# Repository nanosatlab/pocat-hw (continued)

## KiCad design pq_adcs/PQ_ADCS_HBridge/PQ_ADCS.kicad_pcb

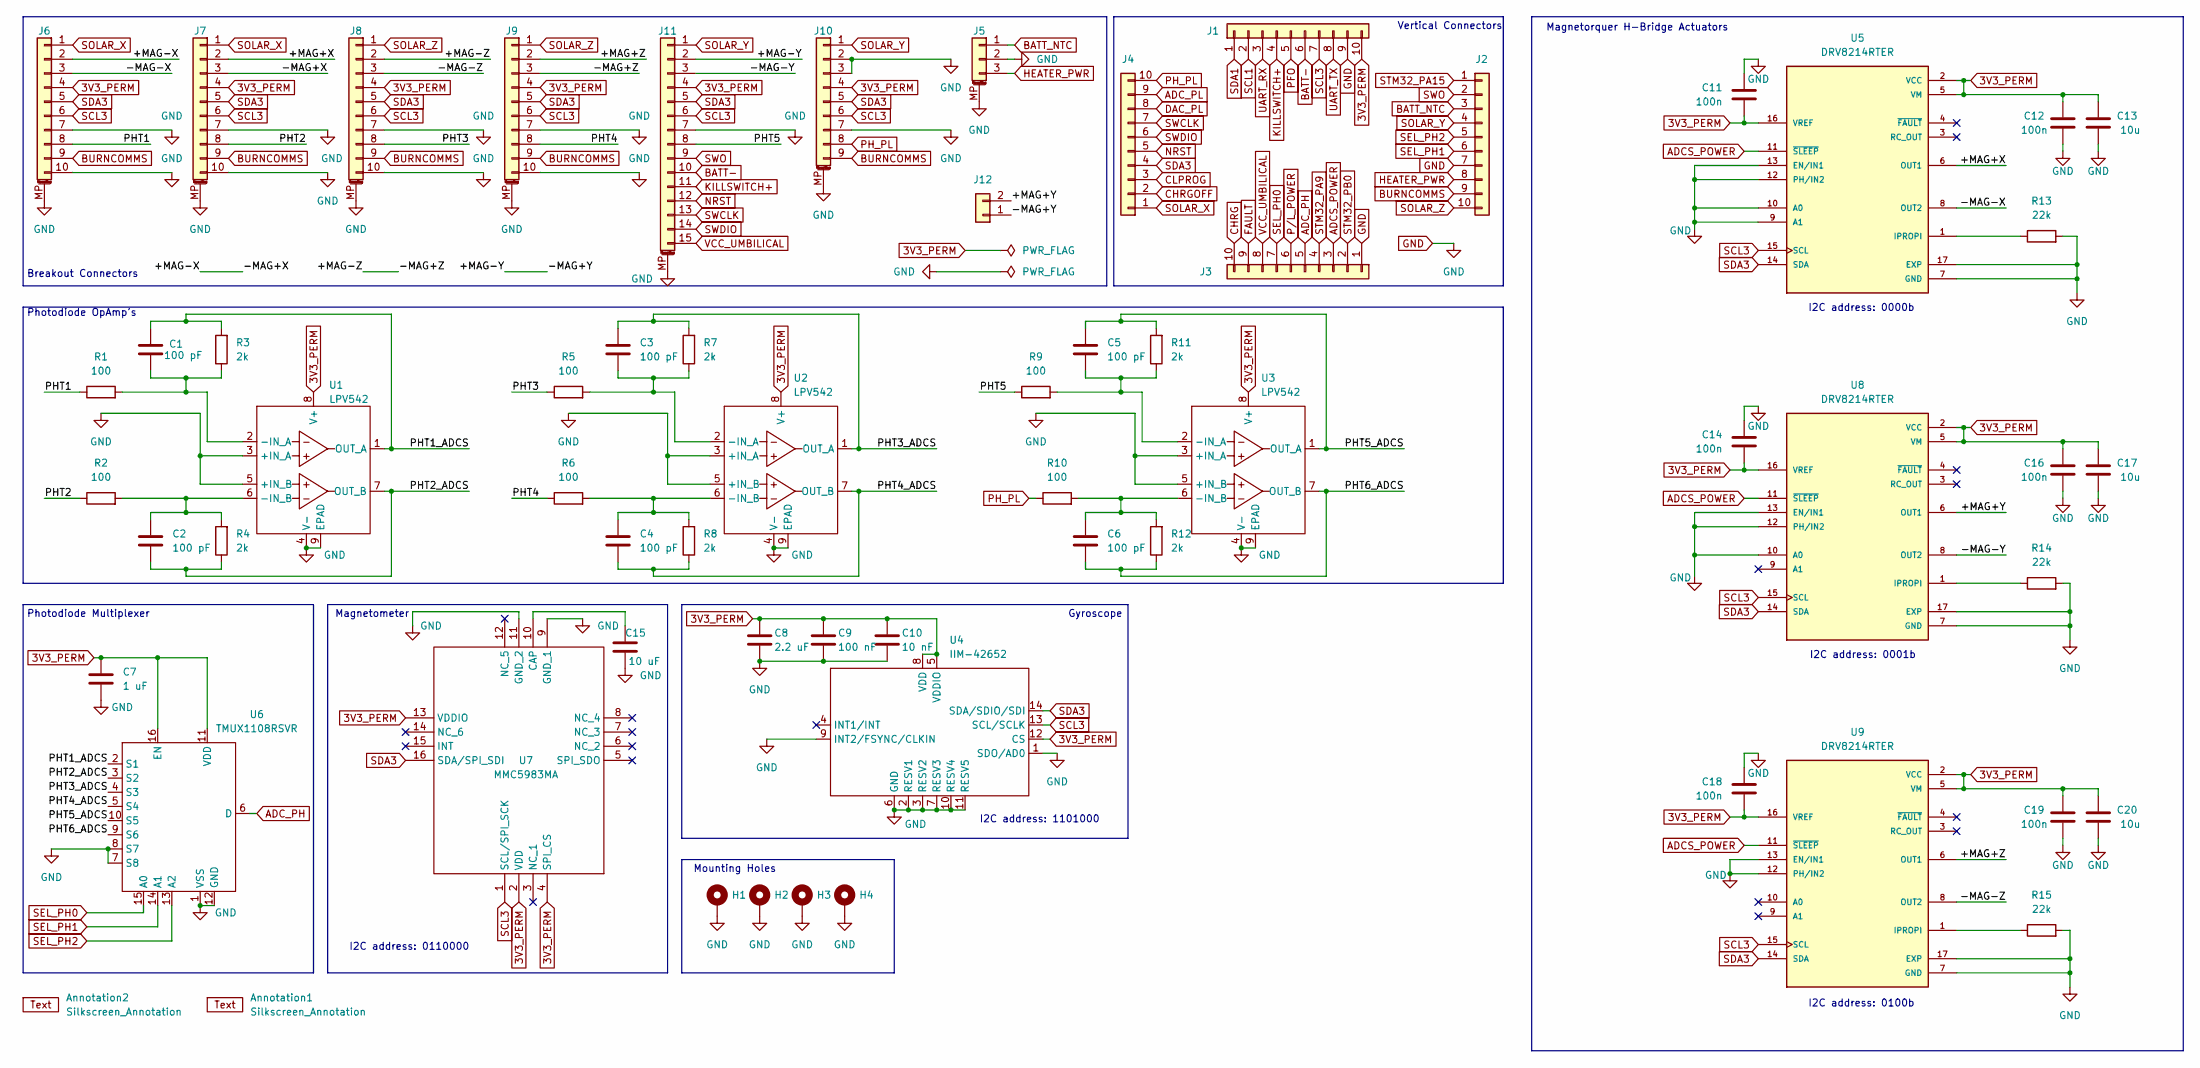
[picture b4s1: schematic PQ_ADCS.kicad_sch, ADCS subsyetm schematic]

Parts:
Annotation1: Silkscreen_Annotation; Bike
Annotation2: Silkscreen_Annotation; Bridgemaker
C1, C2, C3, C4, C5, C6: 100 pF; C_0603_1608Metric; Manufacturer Part Numbe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 06035C101K4T2A
C7: 1 uF; C_0603_1608Metric; Manufacturer Part Numbe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 GRM188R61A105KA61D
C8: 2.2 uF; C_0603_1608Metric; Manufacturer Part Numbe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 GRM033R60J225ME15D
C9: 100 nF; C_0603_1608Metric; Manufacturer Part Numbe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 GRM188R72A104KA35J
C10: 10 nF; C_0603_1608Metric; Manufacturer Part Numbe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 0201YD103KAT4A
C11, C12, C14, C16, C18, C19: 100n; C_0603_1608Metric
C13, C17, C20: 10u; C_0603_1608Metric
C15: 10 uF; C_0805_2012Metric; Manufacturer Part Numbe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 GRM188R72A104KA35J
H1, H2, H3, H4: MountingHole_Pad; MountingHole_3.2mm_M3_Pad; Manufacturer Part Numbe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 N/A
J1, J2, J3, J4: CES-110-02-L-S; SLW-110-01; Manufacturer Part Numbe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 CES-110-02-L-S
J5: Pico-Clasp_01x03; Picoclasp03; Manufacturer Part Numbe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 203556-0307
J6, J7, J8, J9: Pico-Clasp_01x10; Picoclasp10; Manufacturer Part Numbe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 504449-1007
J10: Pico-Clasp_01x09; Picoclasp09; Manufacturer Part Numbe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 504449-0907
J11: Pico-Clasp_01x15; Picoclasp15; Manufacturer Part Numbe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 504449-1507
J12: CES-102-02-L-S; CES-102-02; Manufacturer Part Numbe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 CES-102-02-L-S
R1, R2, R5, R6, R9, R10: 100; R_0603_1608Metric; Manufacturer Part Numbe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 AC0603FR-13100RL
R3, R4, R7, R8, R11, R12: 2k; R_0603_1608Metric; Manufacturer Part Numbe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 RC0603FR-132KL
R13, R14, R15: 22k; R_0603_1608Metric; Manufacturer Part Numbe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 AC0603FR-13100RL
U1, U2, U3: LPV542; TI_X1SON-8_3x3mm; Manufacturer Part Numbe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 LPV542DNXR
U4: IIM-42652; IIM42652; Manufacturer_Part_Number IIM-42652; Mouser Part Number 410-IIM-42652
U5, U8, U9: DRV8214RTER; IC_DRV8214RTER; PARTREV November 2023
U6: TMUX1108RSVR; UQFN-16_1.8x2.6_Pitch0.4mm; Manufacturer Part Numbe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 TMUX1108RSVR
U7: MMC5983MA; Manufacturer_Part_Number MMC5983MA; Mouser Part Number 438-MMC5983MA

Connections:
3V3_PERM: C7.1, C8.1, C9.1, C10.1, C11.2, C12.1, C13.1, C14.2, C16.1, C17.1, C18.2, C19.1, C20.1, J1.10, J6.4, J7.4, J8.4, J9.4, J10.4, J11.4, U1.8 (V+), U2.8 (V+), U3.8 (V+), U4.5 (VDDIO), U4.8 (VDD), U4.12 (CS), U5.2 (VCC), U5.5 (VM), U5.16 (VREF), U6.11 (VDD), U6.16 (EN), U7.2 (VDD), U7.4 (SPI_CS), U7.13 (VDDIO), U8.2 (VCC), U8.5 (VM), U8.16 (VREF), U9.2 (VCC), U9.5 (VM), U9.16 (VREF)
/+MAG+X: J7.2, U5.6 (OUT1)
/+MAG+Y: J12.2, U8.6 (OUT1)
/+MAG+Z: J9.2, U9.6 (OUT1)
/+MAG-X: J6.2, J7.3
/+MAG-Y: J11.2, J12.1
/+MAG-Z: J8.2, J9.3
/-MAG-X: J6.3, U5.8 (OUT2)
/-MAG-Y: J11.3, U8.8 (OUT2)
/-MAG-Z: J8.3, U9.8 (OUT2)
/PHT1: J6.8, R1.1
/PHT1_ADCS: C1.1, R3.2, U1.1 (OUT_A), U6.2 (S1)
/PHT2: J7.8, R2.1
/PHT2_ADCS: C2.2, R4.1, U1.7 (OUT_B), U6.3 (S2)
/PHT3: J8.8, R5.1
/PHT3_ADCS: C3.1, R7.2, U2.1 (OUT_A), U6.4 (S3)
/PHT4: J9.8, R6.1
/PHT4_ADCS: C4.2, R8.1, U2.7 (OUT_B), U6.5 (S4)
/PHT5: J11.8, R9.1
/PHT5_ADCS: C5.1, R11.2, U3.1 (OUT_A), U6.10 (S5)
/PHT6_ADCS: C6.2, R12.1, U3.7 (OUT_B), U6.9 (S6)
ADCS_POWER: J3.3, U5.11 (~SLEEP), U8.11 (~SLEEP), U9.11 (~SLEEP)
ADC_PH: J3.5, U6.6 (D)
ADC_PL: J4.9
BATT-: J1.6, J11.10
BATT_NTC: J2.3, J5.1
BURNCOMMS: J2.9, J6.9, J7.9, J8.9, J9.9, J10.9
CHRG: J3.10
CHRGOFF: J4.2
CLPROG: J4.3
DAC_PL: J4.8
FAULT: J3.9
GND: C7.2, C8.2, C9.2, C10.2, C11.1, C12.2, C13.2, C14.1, C15.2, C16.2, C17.2, C18.1, C19.2, C20.2, H1.1, H2.1, H3.1, H4.1, J1.9, J2.7, J3.1, J5.2, J5.MP, J6.7, J6.10, J6.MP, J7.7, J7.10, J7.MP, J8.7, J8.10, J8.MP, J9.7, J9.10, J9.MP, J10.2, J10.3, J10.7, J10.MP, J11.7, J11.MP, R13.2, R14.2, R15.2, U1.3 (+IN_A), U1.4 (V-), U1.5 (+IN_B), U1.9 (EPAD), U2.3 (+IN_A), U2.4 (V-), U2.5 (+IN_B), U2.9 (EPAD), U3.3 (+IN_A), U3.4 (V-), U3.5 (+IN_B), U3.9 (EPAD), U4.1 (SDO/AD0), U4.2 (RESV1), U4.3 (RESV2), U4.6 (GND), U4.7 (RESV3), U4.9 (INT2/FSYNC/CLKIN), U4.10 (RESV4), U4.11 (RESV5), U5.7 (GND), U5.9 (A1), U5.10 (A0), U5.12 (PH/IN2), U5.13 (EN/IN1), U5.17 (EXP), U6.1 (VSS), U6.7 (S8), U6.8 (S7), U6.12 (GND), U7.9 (GND_1), U7.11 (GND_2), U8.7 (GND), U8.10 (A0), U8.12 (PH/IN2), U8.13 (EN/IN1), U8.17 (EXP), U9.7 (GND), U9.12 (PH/IN2), U9.13 (EN/IN1), U9.17 (EXP)
HEATER_PWR: J2.8, J5.3
KILLSWITCH+: J1.4, J11.11
NRST: J4.5, J11.12
unnamed: C1.2, R1.2, R3.1, U1.2 (-IN_A)
unnamed: C2.1, R2.2, R4.2, U1.6 (-IN_B)
unnamed: C3.2, R5.2, R7.1, U2.2 (-IN_A)
unnamed: C4.1, R6.2, R8.2, U2.6 (-IN_B)
unnamed: C5.2, R9.2, R11.1, U3.2 (-IN_A)
unnamed: C6.1, R10.2, R12.2, U3.6 (-IN_B)
unnamed: R13.1, U5.1 (IPROPI)
unnamed: C15.1, U7.10 (CAP)
unnamed: R14.1, U8.1 (IPROPI)
unnamed: R15.1, U9.1 (IPROPI)
PFO: J1.5
PH_PL: J4.10, J10.8, R10.1
P/L_POWER: J3.6
SCL1: J1.2
SCL3: J1.7, J6.6, J7.6, J8.6, J9.6, J10.6, J11.6, U4.13 (SCL/SCLK), U5.15 (SCL), U7.1 (SCL/SPI_SCK), U8.15 (SCL), U9.15 (SCL)
SDA1: J1.1
SDA3: J4.4, J6.5, J7.5, J8.5, J9.5, J10.5, J11.5, U4.14 (SDA/SDIO/SDI), U5.14 (SDA), U7.16 (SDA/SPI_SDI), U8.14 (SDA), U9.14 (SDA)
SEL_PH0: J3.7, U6.15 (A0)
SEL_PH1: J2.6, U6.14 (A1)
SEL_PH2: J2.5, U6.13 (A2)
SOLAR_X: J4.1, J6.1, J7.1
SOLAR_Y: J2.4, J10.1, J11.1
SOLAR_Z: J2.10, J8.1, J9.1
STM32_PA9: J3.4
STM32_PA15: J2.1
STM32_PB0: J3.2
SWCLK: J4.7, J11.13
SWDIO: J4.6, J11.14
SWO: J2.2, J11.9
UART_RX: J1.3
UART_TX: J1.8
VCC_UMBILICAL: J3.8, J11.15

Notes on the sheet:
I2C address: 0100b
Mounting Holes
Breakout Connectors
I2C address: 1101000
Photodiode Multiplexer
Gyroscope
I2C address: 0000b
I2C address: 0110000
I2C address: 0001b
Photodiode OpAmp's
Magnetorquer H-Bridge Actuators
Vertical Connectors
Magnetometer

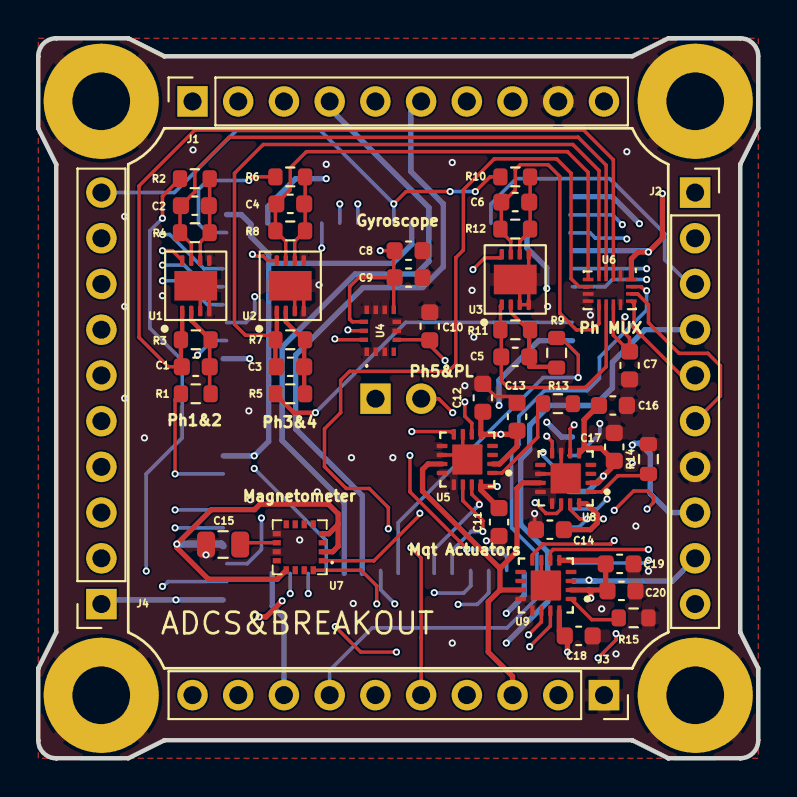
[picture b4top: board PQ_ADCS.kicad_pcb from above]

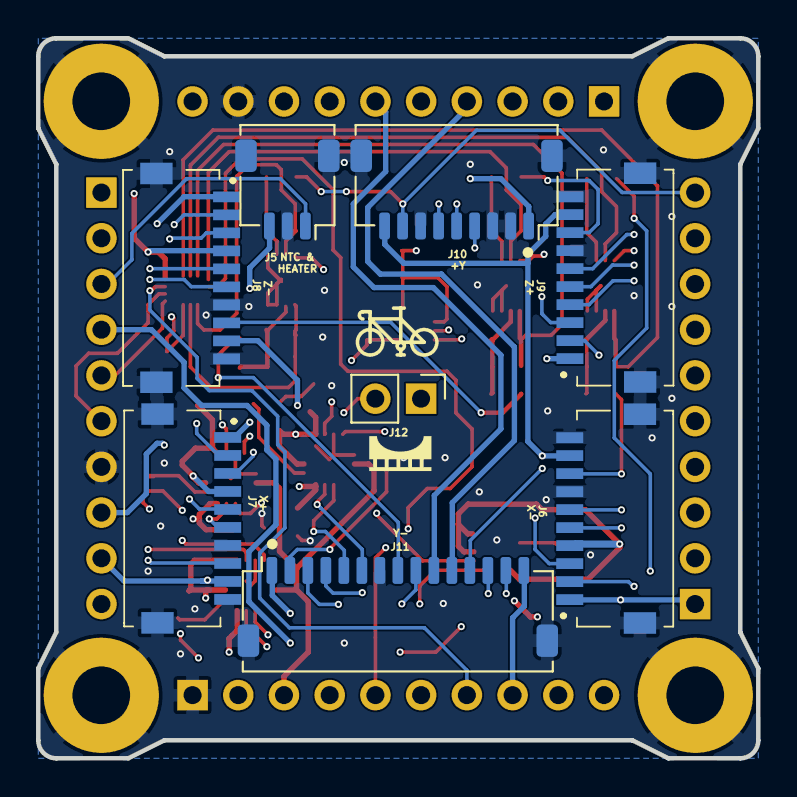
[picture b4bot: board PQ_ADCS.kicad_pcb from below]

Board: 6 copper layers, 40.0 x 40.0 mm, 62 parts (10 on the bottom side), 53 nets.

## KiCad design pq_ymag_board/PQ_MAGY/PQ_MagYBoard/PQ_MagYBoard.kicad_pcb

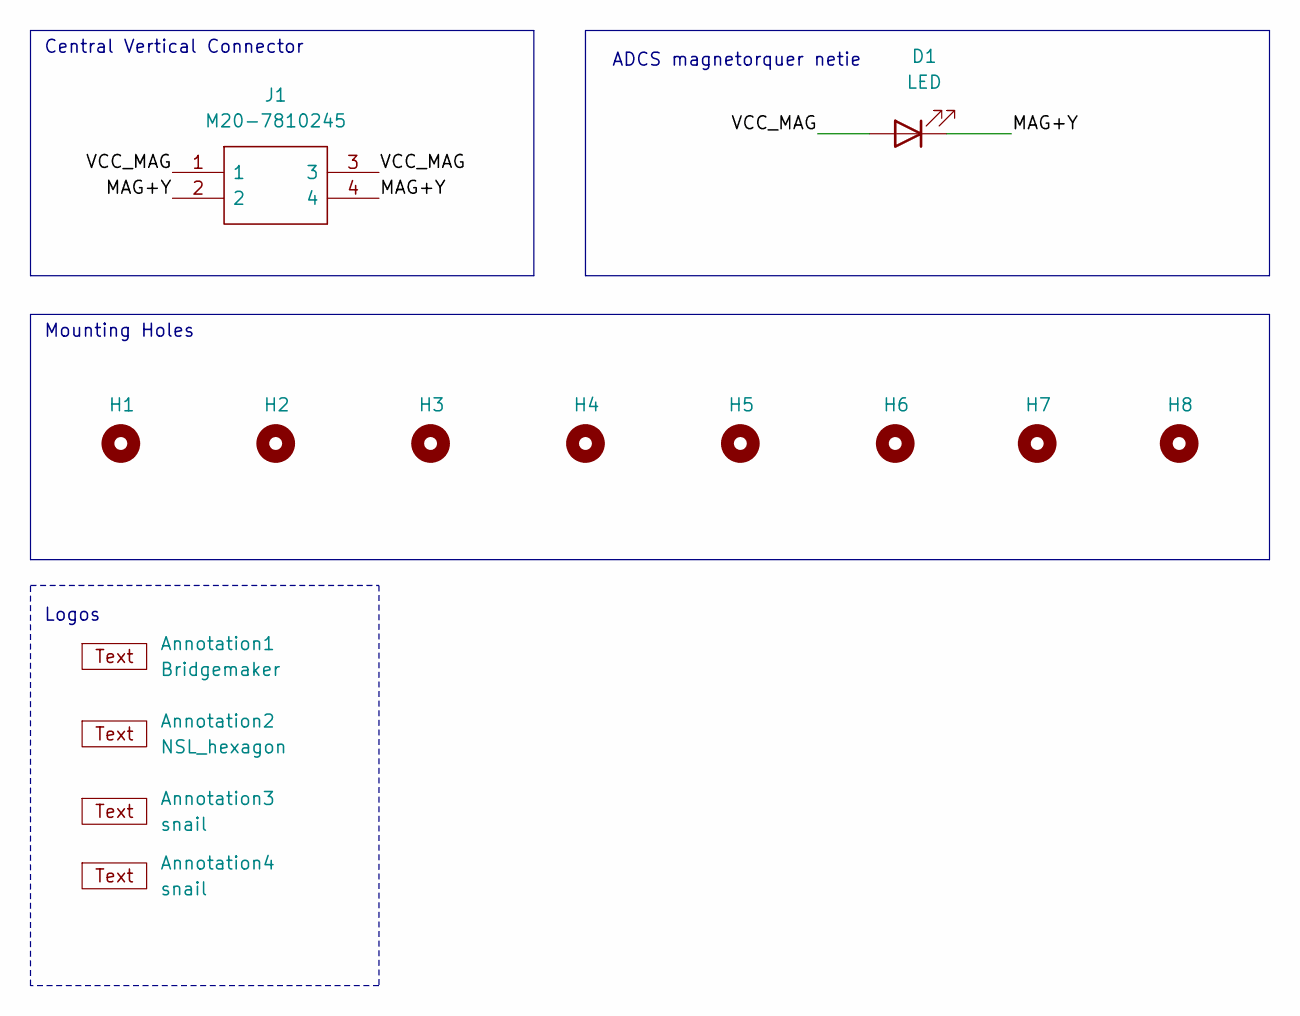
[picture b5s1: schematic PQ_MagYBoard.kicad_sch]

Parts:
Annotation1: Bridgemaker
Annotation2: NSL_hexagon
Annotation3: snail; Snail
Annotation4: snail; pocat_lektron
D1: LED; LED_0402_1005Metric
H1, H2, H3, H4: MountingHole; MountingHole_6.4mm_M6_DIN965
H5, H6, H7, H8: MountingHole; MountingHole_2.2mm_M2_DIN965
J1: M20-7810245; M207810245; Manufacturer_Part_Number M20-7810245; Mouser Part Number 855-M20-7810245

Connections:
/MAG+Y: D1.1 (K), J1.2, J1.4
/VCC_MAG: D1.2 (A), J1.1, J1.3

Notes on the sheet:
Logos
Mounting Holes
ADCS magnetorquer netie
Central Vertical Connector

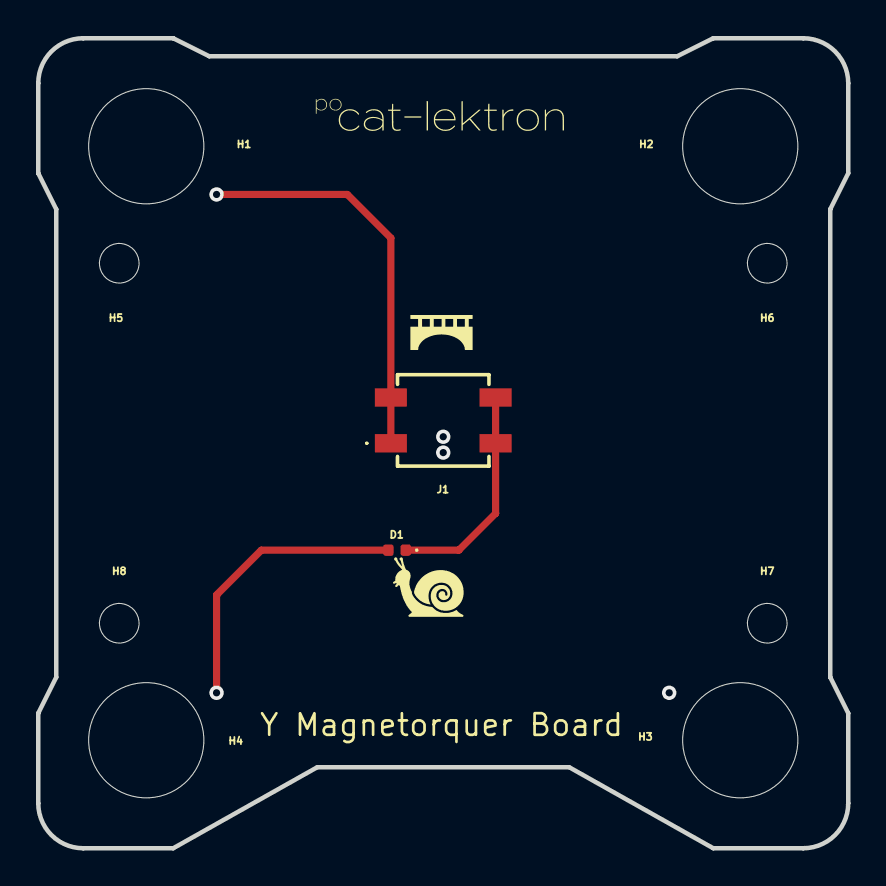
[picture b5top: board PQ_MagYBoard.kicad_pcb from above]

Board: 6 copper layers, 45.0 x 45.0 mm, 14 parts (1 on the bottom side), 2 nets.

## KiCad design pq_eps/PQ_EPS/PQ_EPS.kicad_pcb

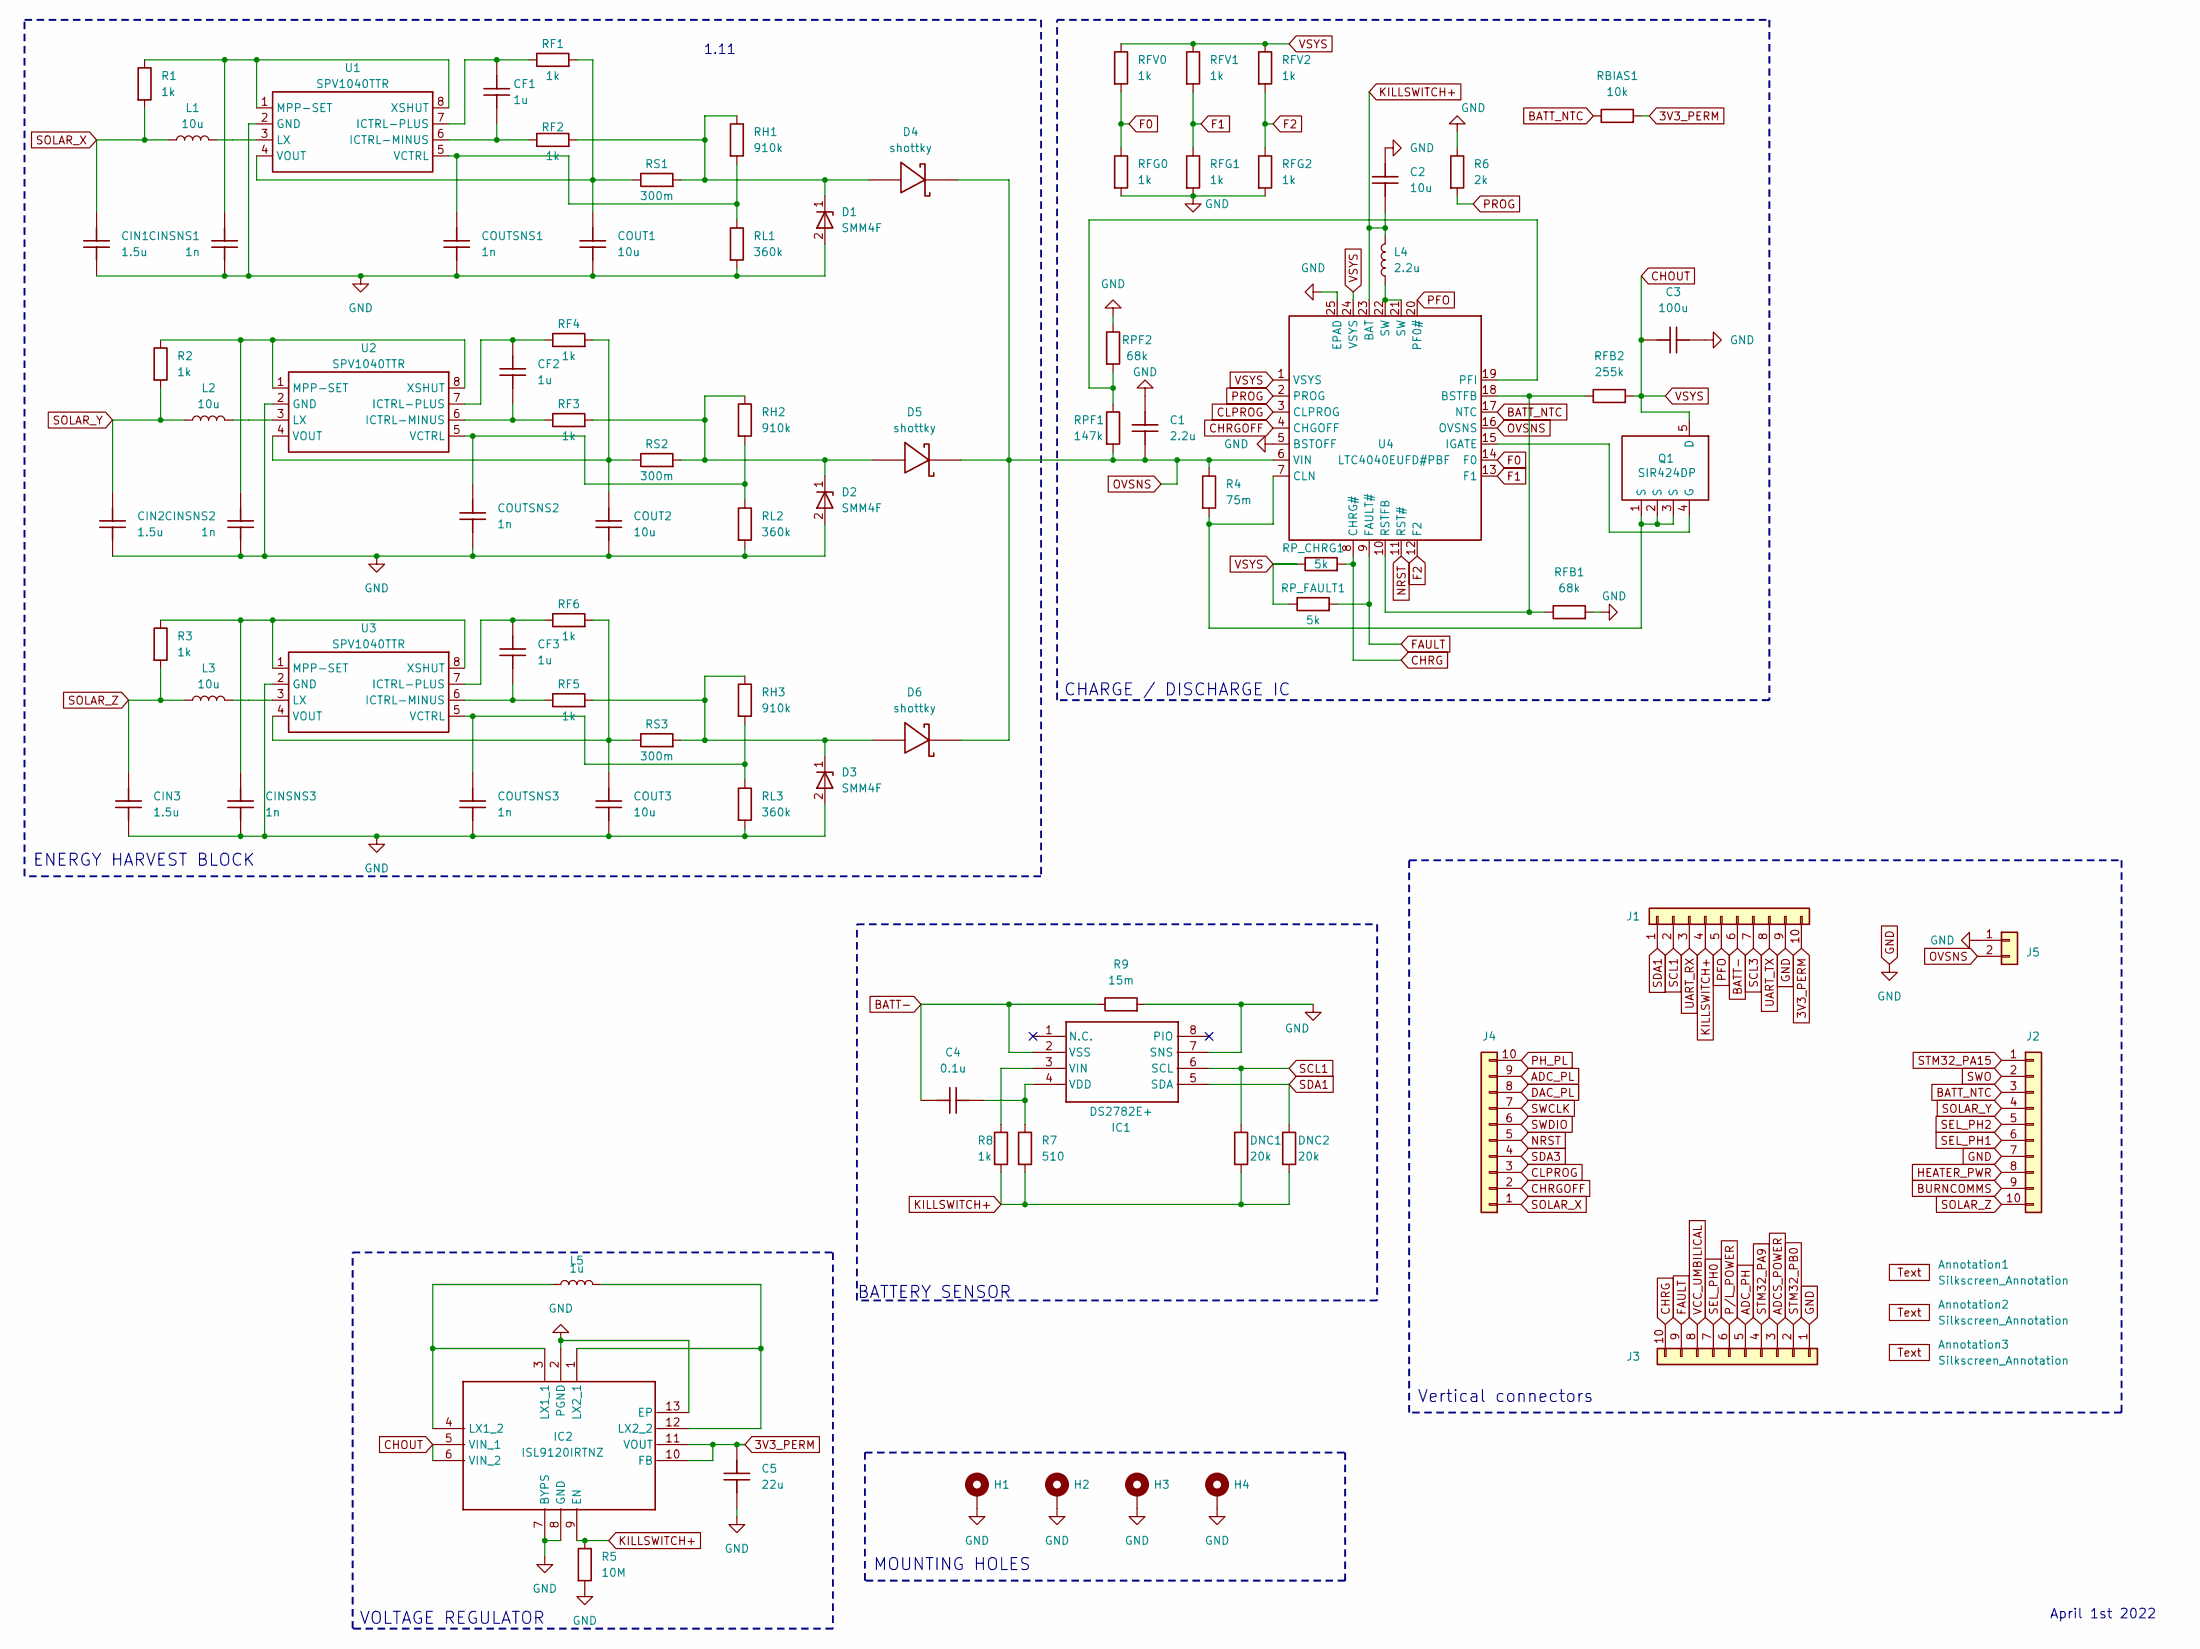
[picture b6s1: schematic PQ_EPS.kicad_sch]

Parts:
Annotation1: Silkscreen_Annotation; Bridgemaker
Annotation2: Silkscreen_Annotation; NakNak
Annotation3: Silkscreen_Annotation; Snail
C1: 2.2u; C_0603_1608Metric; Manufacturer Part Numbe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 GRM155R61C225KE11D
C2: 10u; C_0603_1608Metric; Manufacturer Part Numbe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 GRM188R61A106KAALD
C3: 100u; C_1206_3216Metric; Manufacturer Part Numbe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 GRM21BR60J107ME15K
C4: 0.1u; C_0603_1608Metric; Manufacturer Part Numbe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 C0603C104K8PACTU
C5: 22u; C_0603_1608Metric; Manufacturer Part Numbe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 GRM187R61A226ME15J
CF1, CF2, CF3: 1u; C_0603_1608Metric; Manufacturer Part Numbe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 GRM155R61C105KA12D
CIN1, CIN2, CIN3: 1.5u; C_0603_1608Metric; Manufacturer Part Numbe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 C1005X5R1V155K050BC
CINSNS1, CINSNS2, CINSNS3: 1n; C_0603_1608Metric; Manufacturer Part Numbe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 GRM155R61A102KA01D
COUT1, COUT2, COUT3: 10u; C_0603_1608Metric; Manufacturer Part Numbe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 GRM188R61A106KAALD
COUTSNS1, COUTSNS2, COUTSNS3: 1n; C_0603_1608Metric; Manufacturer Part Numbe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 GRM155R61A102KA01D
D1, D2, D3: SMM4F; SMM4F15ATR; Manufacturer Part Numbe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 SMM4F18A-TR
D4, D5, D6: shottky; RBS1LAM40ATR_Schottky; Manufacturer Part Numbe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 RBS1LAM40ATR
DNC1, DNC2: 20k; R_0603_1608Metric; Manufacturer Part Numbe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 ERJ-UP3J203V
H1, H2, H3, H4: MountingHole_Pad; MountingHole_3.2mm_M3_Pad; Manufacturer Part Numbe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 N/A
IC1: DS2782E+; TSSOP-8_4.4x3mm_P0.65mm; Manufacturer Part Numbe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 DS2782E+
IC2: ISL9120IRTNZ; Manufacturer Part Numbe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 ISL9120IRTNZ
J1, J2, J3, J4: CES-110-02-L-S; SLW-110-01; Manufacturer Part Numbe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 CES-110-02-L-S
J5: CES-102-02
L1, L2, L3: 10u; L_0805_2012Metric; Manufacturer Part Numbe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 LQH2MPZ100MGRL
L4: 2.2u; XAL5030222MEC; Manufacturer_Part_Number XAL5030-222MEC; Mouser Part Number 994-XAL5030-222MEC
L5: 1u; L_0805_2012Metric; Manufacturer Part Numbe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 TFM201610GHM1R0A
Q1: SIR424DP; Manufacturer Part Numbe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 SIR424DP-T1-GE3
R1, R2, R3, R8: 1k; R_0603_1608Metric
R4: 75m; R_0805_2012Metric; Manufacturer Part Numbe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 UR73V2ATTD75L0F
R5: 10M; R_0805_2012Metric; Manufacturer Part Numbe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 UR73V2ATTD75L0F
R6: 2k; R_0603_1608Metric
R7: 510; R_0603_1608Metric
R9: 15m; R_0603_1608Metric
RBIAS1: 10k; R_0603_1608Metric
RF1, RF2, RF3, RF4, RF5, RF6: 1k; R_0603_1608Metric; Manufacturer Part Numbe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 CRCW04021K00FKEDHP
RFB1: 68k; R_0603_1608Metric; Manufacturer Part Numbe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 SG73P1ETTP6802F
RFB2: 255k; R_0402_1005Metric; Manufacturer Part Numbe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 ERJ-U02F2553X
RFG0, RFG1, RFG2: 1k; R_0603_1608Metric; Manufacturer Part Numbe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 PCAN0805E1001BST5
RFV0, RFV1, RFV2: 1k; R_0603_1608Metric; Manufacturer Part Numbe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 PCAN0805E1001BST5
RH1, RH2, RH3: 910k; R_0603_1608Metric; Manufacturer Part Numbe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 ERJ-PA3F9103V
RL1, RL2, RL3: 360k; R_0603_1608Metric; Manufacturer Part Numbe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 ERJ-UP3F3603V
RPF1: 147k; R_0603_1608Metric; Manufacturer Part Numbe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 ERJ-P03F1473V
RPF2: 68k; R_0603_1608Metric; Manufacturer Part Numbe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 SG73P1ETTP6802F
RP_CHRG1: 5k; R_0805_2012Metric; Manufacturer Part Numbe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 CRCW08055K00JNTA
RP_FAULT1: 5k; R_0805_2012Metric; Manufacturer Part Numbe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 CRCW08055K00JNTA
RS1, RS2, RS3: 300m; R_0603_1608Metric; Manufacturer Part Numbe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 UCR03EVPFLR300
U1, U2, U3: SPV1040TTR; TSSOP-8_4.4x3mm_P0.65mm; Manufacturer Part Numbe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 SPV1040TTR
U4: LTC4040EUFD#PBF; QFN-24-1EP_4x5mm_P0.5mm_EP2.65x3.65mm; Manufacturer Part Numbe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 LTC4040IUFD#PBF

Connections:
3V3_PERM: C5.2, IC2.10 (FB), IC2.11 (VOUT), J1.10, RBIAS1.2
ADCS_POWER: J3.3
ADC_PH: J3.5
ADC_PL: J4.9
BATT-: C4.2, IC1.2 (VSS), J1.6, R9.1
BATT_NTC: J2.3, RBIAS1.1, U4.17 (NTC)
BURNCOMMS: J2.9
CHOUT: C3.1, IC2.5 (VIN_1), IC2.6 (VIN_2), Q1.5 (D), RFB2.2, RFV0.1, RFV1.1, RFV2.1, RP_CHRG1.1, RP_FAULT1.1, U4.1 (VSYS), U4.24 (VSYS)
CHRG: J3.10, RP_CHRG1.2, U4.8 (CHRG#)
CHRGOFF: J4.2, U4.4 (CHGOFF)
CLPROG: J4.3, U4.3 (CLPROG)
DAC_PL: J4.8
F0: RFG0.1, RFV0.2, U4.14 (F0)
F1: RFG1.1, RFV1.2, U4.13 (F1)
F2: RFG2.1, RFV2.2, U4.12 (F2)
FAULT: J3.9, RP_FAULT1.2, U4.9 (FAULT#)
GND: C1.2, C2.2, C3.2, C5.1, CIN1.1, CIN2.1, CIN3.1, CINSNS1.1, CINSNS2.1, CINSNS3.1, COUT1.1, COUT2.1, COUT3.1, COUTSNS1.1, COUTSNS2.1, COUTSNS3.1, D1.2, D2.2, D3.2, H1.1, H2.1, H3.1, H4.1, IC1.7 (SNS), IC2.2 (PGND), IC2.7 (BYPS), IC2.8 (GND), IC2.13 (EP), J1.9, J2.7, J3.1, J5.1, R5.2, R6.1, R9.2, RFB1.2, RFG0.2, RFG1.2, RFG2.2, RL1.2, RL2.2, RL3.2, RPF2.1, U1.2 (GND), U2.2 (GND), U3.2 (GND), U4.5 (BSTOFF), U4.25 (EPAD)
HEATER_PWR: J2.8
KILLSWITCH+: C2.1, DNC1.2, DNC2.2, IC2.9 (EN), J1.4, L4.2, R5.1, R7.2, R8.2, U4.23 (BAT)
NRST: J4.5, U4.11 (RST#)
unnamed: D1.1, D4.2, RF2.2, RH1.1, RS1.2
unnamed: D2.1, D5.2, RF3.2, RH2.1, RS2.2
unnamed: D3.1, D6.2, RF5.2, RH3.1, RS3.2
unnamed: C4.1, IC1.4 (VDD), R7.1
unnamed: IC1.3 (VIN), R8.1
unnamed: IC2.3 (LX1_1), IC2.4 (LX1_2), L5.1
unnamed: IC2.1 (LX2_1), IC2.12 (LX2_2), L5.2
unnamed: L4.1, U4.21 (SW), U4.22 (SW)
unnamed: Q1.4 (G), U4.15 (IGATE)
unnamed: CF1.1, RF2.1, U1.6 (ICTRL-MINUS)
unnamed: CF1.2, RF1.1, U1.7 (ICTRL-PLUS)
unnamed: L1.1, U1.3 (LX)
unnamed: CINSNS1.2, R1.1, U1.1 (MPP-SET), U1.8 (XSHUT)
unnamed: COUTSNS1.2, RH1.2, RL1.1, U1.5 (VCTRL)
unnamed: COUT1.2, RF1.2, RS1.1, U1.4 (VOUT)
unnamed: CF2.1, RF3.1, U2.6 (ICTRL-MINUS)
unnamed: CF2.2, RF4.1, U2.7 (ICTRL-PLUS)
unnamed: L2.2, U2.3 (LX)
unnamed: CINSNS2.2, R2.1, U2.1 (MPP-SET), U2.8 (XSHUT)
unnamed: COUTSNS2.2, RH2.2, RL2.1, U2.5 (VCTRL)
unnamed: COUT2.2, RF4.2, RS2.1, U2.4 (VOUT)
unnamed: CF3.1, RF5.1, U3.6 (ICTRL-MINUS)
unnamed: CF3.2, RF6.1, U3.7 (ICTRL-PLUS)
unnamed: L3.2, U3.3 (LX)
unnamed: CINSNS3.2, R3.1, U3.1 (MPP-SET), U3.8 (XSHUT)
unnamed: COUTSNS3.2, RH3.2, RL3.1, U3.5 (VCTRL)
unnamed: COUT3.2, RF6.2, RS3.1, U3.4 (VOUT)
unnamed: RFB1.1, RFB2.1, U4.10 (RSTFB), U4.18 (BSTFB)
unnamed: Q1.1 (S), Q1.2 (S), Q1.3 (S), R4.2, U4.7 (CLN)
unnamed: RPF1.1, RPF2.2, U4.19 (PFI)
OVSNS: C1.1, D4.1, D5.1, D6.1, J5.2, R4.1, RPF1.2, U4.6 (VIN), U4.16 (OVSNS)
PFO: J1.5, U4.20 (PF0#)
PH_PL: J4.10
PROG: R6.2, U4.2 (PROG)
P/L_POWER: J3.6
SCL1: DNC1.1, IC1.6 (SCL), J1.2
SCL3: J1.7
SDA1: DNC2.1, IC1.5 (SDA), J1.1
SDA3: J4.4
SEL_PH0: J3.7
SEL_PH1: J2.6
SEL_PH2: J2.5
SOLAR_X: CIN1.2, J4.1, L1.2, R1.2
SOLAR_Y: CIN2.2, J2.4, L2.1, R2.2
SOLAR_Z: CIN3.2, J2.10, L3.1, R3.2
STM32_PA9: J3.4
STM32_PA15: J2.1
STM32_PB0: J3.2
SWCLK: J4.7
SWDIO: J4.6
SWO: J2.2
UART_RX: J1.3
UART_TX: J1.8
VCC_UMBILICAL: J3.8

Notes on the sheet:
ENERGY HARVEST BLOCK
Vertical connectors
MOUNTING HOLES
VOLTAGE REGULATOR
CHARGE / DISCHARGE IC
BATTERY SENSOR
April 1st 2022
1.11

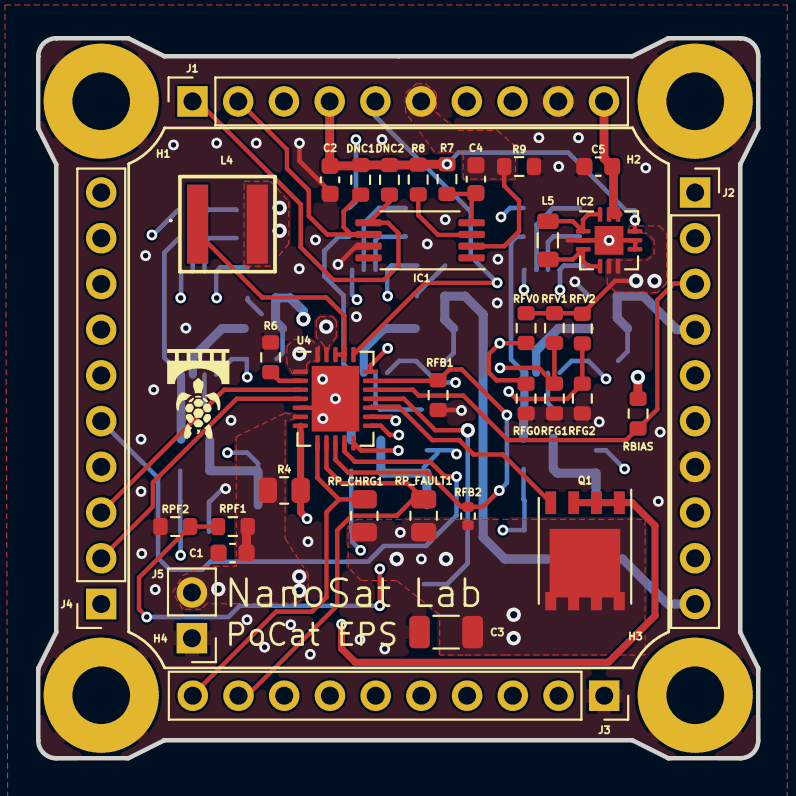
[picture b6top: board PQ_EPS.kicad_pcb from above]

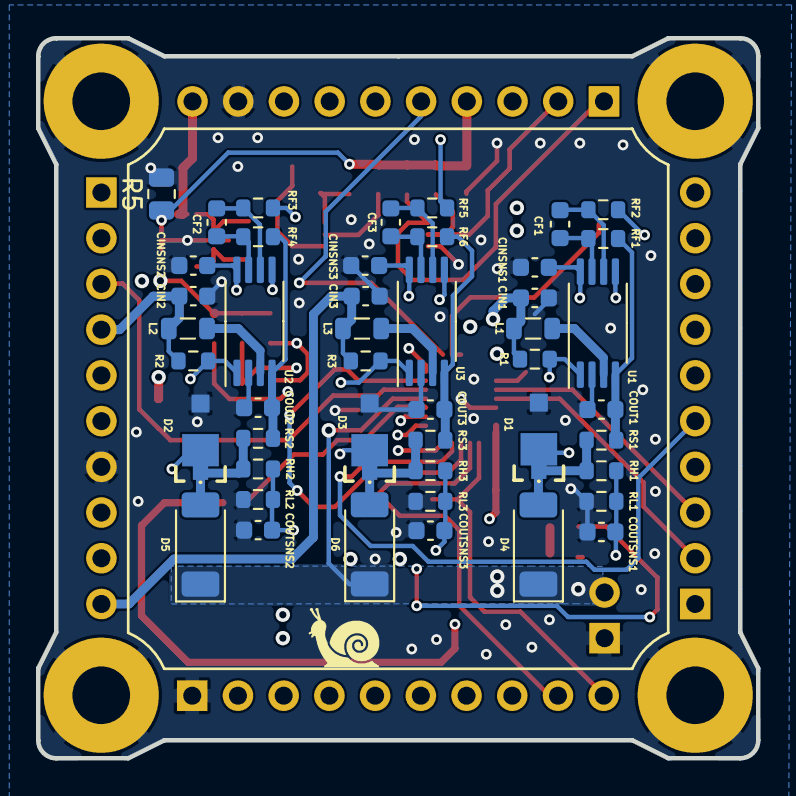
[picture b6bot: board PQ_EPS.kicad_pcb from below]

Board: 4 copper layers, 40.0 x 40.0 mm, 89 parts (47 on the bottom side), 52 nets.

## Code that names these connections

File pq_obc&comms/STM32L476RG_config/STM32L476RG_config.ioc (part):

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Mcu.Name=STM32L476R(C-E-G)Tx
Mcu.Package=LQFP64
Mcu.UserName=STM32L476RGTx
PA1.Signal=ADCx_IN6
PA10.Signal=GPIO_Output
PA11.Signal=GPIO_Output
PA12.Signal=GPIO_Output
PA13\ (JTMS-SWDIO).Mode=Serial_Wire
PA13\ (JTMS-SWDIO).Signal=SYS_JTMS-SWDIO
PA14\ (JTCK-SWCLK).Mode=Serial_Wire
PA14\ (JTCK-SWCLK).Signal=SYS_JTCK-SWCLK
PA4.Signal=ADCx_IN9
PA5.Signal=COMP_DAC12_group
PA6.Signal=ADCx_IN11
PA7.Signal=ADCx_IN12
PA8.Signal=GPIO_Input
PA9.Signal=GPIO_Output
PB0.Signal=GPIO_Output
PB1.Signal=ADCx_IN16
PB10.Signal=GPIO_Output
PB11.Signal=GPXTI11
PB12.Mode=NSS_Signal_Hard_Output
PB12.Signal=SPI2_NSS
PB13.Mode=Full_Duplex_Master
PB13.Signal=SPI2_SCK
PB14.Mode=Full_Duplex_Master
PB14.Signal=SPI2_MISO
PB15.Mode=Full_Duplex_Master
PB15.Signal=SPI2_MOSI
PB2.Signal=GPIO_Input
PB5.Signal=GPIO_Input
PB6.Mode=I2C
PB6.Signal=I2C1_SCL
PB7.Mode=I2C
PB7.Signal=I2C1_SDA
PC0.Signal=GPIO_Output
PC10.Mode=Asynchronous
PC10.Signal=UART4_TX
PC11.Mode=Asynchronous
PC11.Signal=UART4_RX
PC14-OSC32_IN\ (PC14).Mode=LSE-External-Oscillator
PC14-OSC32_IN\ (PC14).Signal=RCC_OSC32_IN
PC15-OSC32_OUT\ (PC15).Mode=LSE-External-Oscillator
PC15-OSC32_OUT\ (PC15).Signal=RCC_OSC32_OUT
PC2.Signal=GPIO_Output
PC3.Signal=GPIO_Output
PC4.Signal=GPIO_Input
PC9.Signal=GPIO_Output
PH0-OSC_IN\ (PH0).Mode=HSE-External-Oscillator
PH0-OSC_IN\ (PH0).Signal=RCC_OSC_IN
PH1-OSC_OUT\ (PH1).Mode=HSE-External-Oscillator
PH1-OSC_OUT\ (PH1).Signal=RCC_OSC_OUT
RCC.HSE_VALUE=8000000
board=custom

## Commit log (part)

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2022-10-06 project structure
2022-10-07 ocb&comms ported to KiCad
2022-10-08 ADCS&Breackout Board ported to KiCad
2022-10-10 identified magnetorquer actuators
2022-10-28 change organization
2022-10-28 reorganization
2022-10-28 OBC changed to STM32L4, pinout added, EPS ported
2022-10-29 eps port to kicad corrected
2022-10-31 Whatever
2022-10-31 hw revision, notes in MoM 09/11/2022
2022-10-31 gitkeep added to empty folders
2022-11-03 hw revision of OBC
2022-11-03 Cleanup!
2022-11-03 fuck txt :)
2022-11-04 obc rework
2022-11-07 OBC board revision 3 finished
2022-11-08 added PA3 pin to pinout
2022-11-09 shitty changes
2022-11-09 OBC finished, BoM included and RF traces revised
2022-11-11 RIP Stefan in NSL
2022-11-15 BoM added to schematic
2022-11-16 Regal per Guillem
2022-11-17 lateral boards added, ADCS schematic lacks mtq drivers
2022-11-17 designs updated
2022-11-21 lots of changes
2022-11-21 adcs board ready for manufacturing
2022-11-21 killswitch and batt- pins swapped
2022-11-22 files changed
2022-11-23 MTQ driver's enable connected to VCC_ADCS
2022-11-25 Lateral, Bottom and MagY boards done
2022-11-29 Assembly update
2023-01-24 document formating
2023-01-25 Revised schematic 25 jan
2023-01-30 EPS LTC 4040 correction and layout revamp
2023-01-30 EPS board revised and Guillem approved
2023-01-31 ADCS: added magnetometer, removed Tsens. OBC: Total_Current net removed, Bat_NTC routed to PA0 OBC ADC input. Ymag: centering of the vertical pin
2023-02-03 Functional revision and finishing touches part I
2023-02-06 Functional revision and finishing touches part II
2023-02-13 Solved old design components&library altium import problems. Pre KiCad7
2023-02-17 Full Kicad7 transition, library improvement and adaptation, correct footprints and 3D models added
2023-03-20 Added adaptive resistive network for battery chemistry and charge voltage flexibility & connected all the PoLs + COMMS to 3V3_perm instead of VCC (3.3V - schottky diode)
2023-03-20 P/L2 V03 final schematic. Replaced the Mixer+VCO+Opamp <- OBC DAC configuration with the MAX2121. Switched the IF from 40 MHz (prone to image frequencies due to passive mixers) to 70 MHz with complex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
2023-03-22 PoL & SX1262 feeding at 3.3V and OBC feeding at 3.1 (Schottky diode) strategy changed from inner layer 2 plane to 1 mm thick traces
2023-03-23 Vertical Pins silkscreen numbering made visible
2023-03-23 P/L2 schematic revision and preliminary layout formulation: tranmission lines and block biasing
2023-03-28 pl1 ready to manufacture, obc&comms small touches prior to manufacture
2023-03-28 Old schematic revision. Floating pin for the EN pin of the Mag Actuator
2023-03-29 Payload 2 Schematic and PCB update. Pedning final verification and manufacturing
2023-03-29 Payload 1 board vertical connector silkscreen annotation correction
2023-03-29 Finished Payload 2 Schematic + PCB + BOM + Gerber + STEP Version 3.0
2023-03-29 Payload 2 V3.1 - Added photodiode, associated Opamp and routing to pin STM PB0
2023-03-29 Payload 2 V3.2 - Rounded the RF 90 degree turn between the C3 and J8 probe connector
2023-03-31 fabrication
2023-03-31 fabrication ready
2023-04-11 Small changes of component fields for the BOM
2023-04-13 BOM creation schematic changes 2.0
2023-04-23 J4 pin was inversed, and traces connected wrongly. Now it is correct. Reorder is needed. F in chat
2023-04-24 Added MPPT input pin for testing on board of the EGSE of the PQ nominal operation: Battery and MPPT input both in use
2023-07-19 opamp footprint and connections corrected
2023-10-04 Added BOM file to P/L2 project
2023-10-04 Updated outer boards design as required by the change from Azur Space house-cut solar cells to Lighttricity's S3040_CIC model. Preserved the older design in lat_board_old
2023-10-11 Updated Production files for the ADCS, LAT and BOT boards for new order
2023-10-17 added MAG addr
2023-11-07 Corrected the PL2 5V booster issue (changed the pins of the LT3048-5 to LT3048 & added resistive divider for 5V output)
2024-01-08 added production in gitignore
2024-01-08 assembly improvements
2024-01-09 step and files created for all subsystems
2024-01-09 added silkscreens for CAD
2024-01-10 pl3 top board step file
2024-01-10 support fr4 step file
2024-01-10 added CAD assembly with PQ1 and PQ3 configurations
2024-01-10 added PQ1 stowed configuration
2024-01-12 solved collission in PL1
2024-01-12 solved wrong connector in lateral board
2024-01-12 fixed PL1 and lateral U.FL connector
2024-04-10 Corrected the U.FL connector footprints on the PL2 Board. Added OBC&COMMS Bom
2024-04-11 Add names of PQ collaborators in Y magnetorquer
2024-04-11 fix mirroring of Lightricity's solar cells
2024-04-11 fix the mirror on the external crystal of the OBC
2024-04-17 ADCS update
    ADCS with magnetometer issue fixed
2024-04-17 add names, bigger hole and mirror solar cell
2024-04-17 Delete PQ_Lat_Board directory
    Error: Incorrect directory added within an incorrect directory.
2024-04-27 PQ EGSE
2024-06-10 Symbol path corrections, X1 crystal mirror correction, J2&J3&J4 name flip PCB
2024-06-10 Altium symbol imports fix, rotated J3, updated track widths for power lines, solved courtyard conflicts, DRC
2024-06-10 Solved symbol conflicts with old Altium path: U1, U2, U3, J1(7) NC, solved symbol-library-footprint conflicts, reduced number of layers from 6 to 4, reduced GND plane zones from 3 to 1 for all layers
2024-06-10 J2(2) pin rename to SWO; DRC
2024-06-10 J2(2) pin rename to SWO; DRC, fixed missconnection of VGA power to P/L_power pin instead of the generic 3V3_perm
2024-06-10 Added NSL lektron logo, reconciled library symbol - footprints, moved the picoblade connector so not to conflict with the top structure, fixed VCC trace issue
2024-06-10 Removed netie, reordered names, added diacritics, added NSL hexagonal logo
2024-06-10 Removed netie, updated SC footprint, trace reform, logo&name cleanup, footprint reconciled, DRC
2024-06-10 Removed netie, updated SC footprint, trace reform, logo&name cleanup, footprint reconciled, DRC, centered umbilical connector
2024-06-11 Fabrication files generated, deprecated file supports removed, (possibly) last order incoming
2024-06-13 Added a charging protection for the battery using the umbilical (antireturn Schottky diode and LDO) and regenerated the production files
2024-07-13 Vitrina PQ
2024-07-13 add MGSE for VGA PQ assembly procedure
2024-07-13 add DXF file for laser cutting acrylic
2024-09-28 Pinout changed in OBC and ADCS
    SCL3 moved to NC
    SCL3 is now PH_PL
2024-10-06 change C15 package from 0603 to 0805
2024-10-06 Recenter components to fit inside the square hole of the slider, change PicoBlade from 2 pins to 3 pins
2024-10-08 Re-routed the SC, added new SC symbol in schematic, and added pad to solder the comms antenna inside the lateral.
2024-10-11 add positive pad behind the Solar Cell to allow soldering the solar cell with epoxy
2024-10-11 add Lighticity SC to bottom with the option to solder using epoxy
2024-10-11 adjust killswitches holes to better align bottom with slider deployer PCB
2024-10-19 PL2 Modifications added
    Phtodiode ampllifier deleted
    Pins restructured
2024-10-21 Recenter holes in Lateral PCB as there was a slight misalignment with the top structure
2024-10-21 small changes: change ID R5 to Rbias, add snail logo, and swap SOLARZ with GND
2024-10-21 swap SOLARZ with GND
2024-10-21 change pin RST_DRIVERS to STM32_PA9, swap SCL3 with NC and redirect all IC to new SCL3 location. Change NC pin to PH_PL, substitute PHT6 to PH_PL and small fixes
2024-10-21 change RST_DRIVERS to STM32_PA9, swap SCL3 with NC, and change NC to PH_PL
2024-10-21 change RST_DRIVERS to STM32_PA9, swap SCL3 with NC and change NC to PH_PL
2024-10-22 add more names
2024-10-23 recover the 6 layers ADCS from older versions
2024-10-23 add missing component names and relocate others
2024-10-30 Cambiar etiquetas de red a etiquetas globales (Major RID 66)
2025-08-01 Clean up repo
2025-08-31 Changes to holes done
2025-11-16 PQ_ADCS_HBridge Add
2025-11-20 H-Bridge Chips Update
2025-11-27 PCB Update
2025-11-30 Reduced errors
2025-12-27 Restart
2025-12-27 EPS changes in progress. Will change to a new implementation
2025-12-27 EPS Changes done. Voltage Regulator ENABLED by Killswitch+
2025-12-27 Great advance
2025-12-27 No errors, but still warnings
2025-12-29 MOdifying connectors ADCS H - Bridge
2025-12-29 lateral modification
2026-01-20 lateral fixed
2026-01-20 LAteral no photodiode finished
2026-01-21 Removed photodiode botboard
2026-01-21 Removed photodiode +Y magnetorquer PCB
2026-03-15 Hbridge
2026-03-19 Trying to add connectors bottom ADCS PCB
2026-05-18 ADCS_HBRIDGE backup restore
    Restored version with H bridge and no connectors modification
